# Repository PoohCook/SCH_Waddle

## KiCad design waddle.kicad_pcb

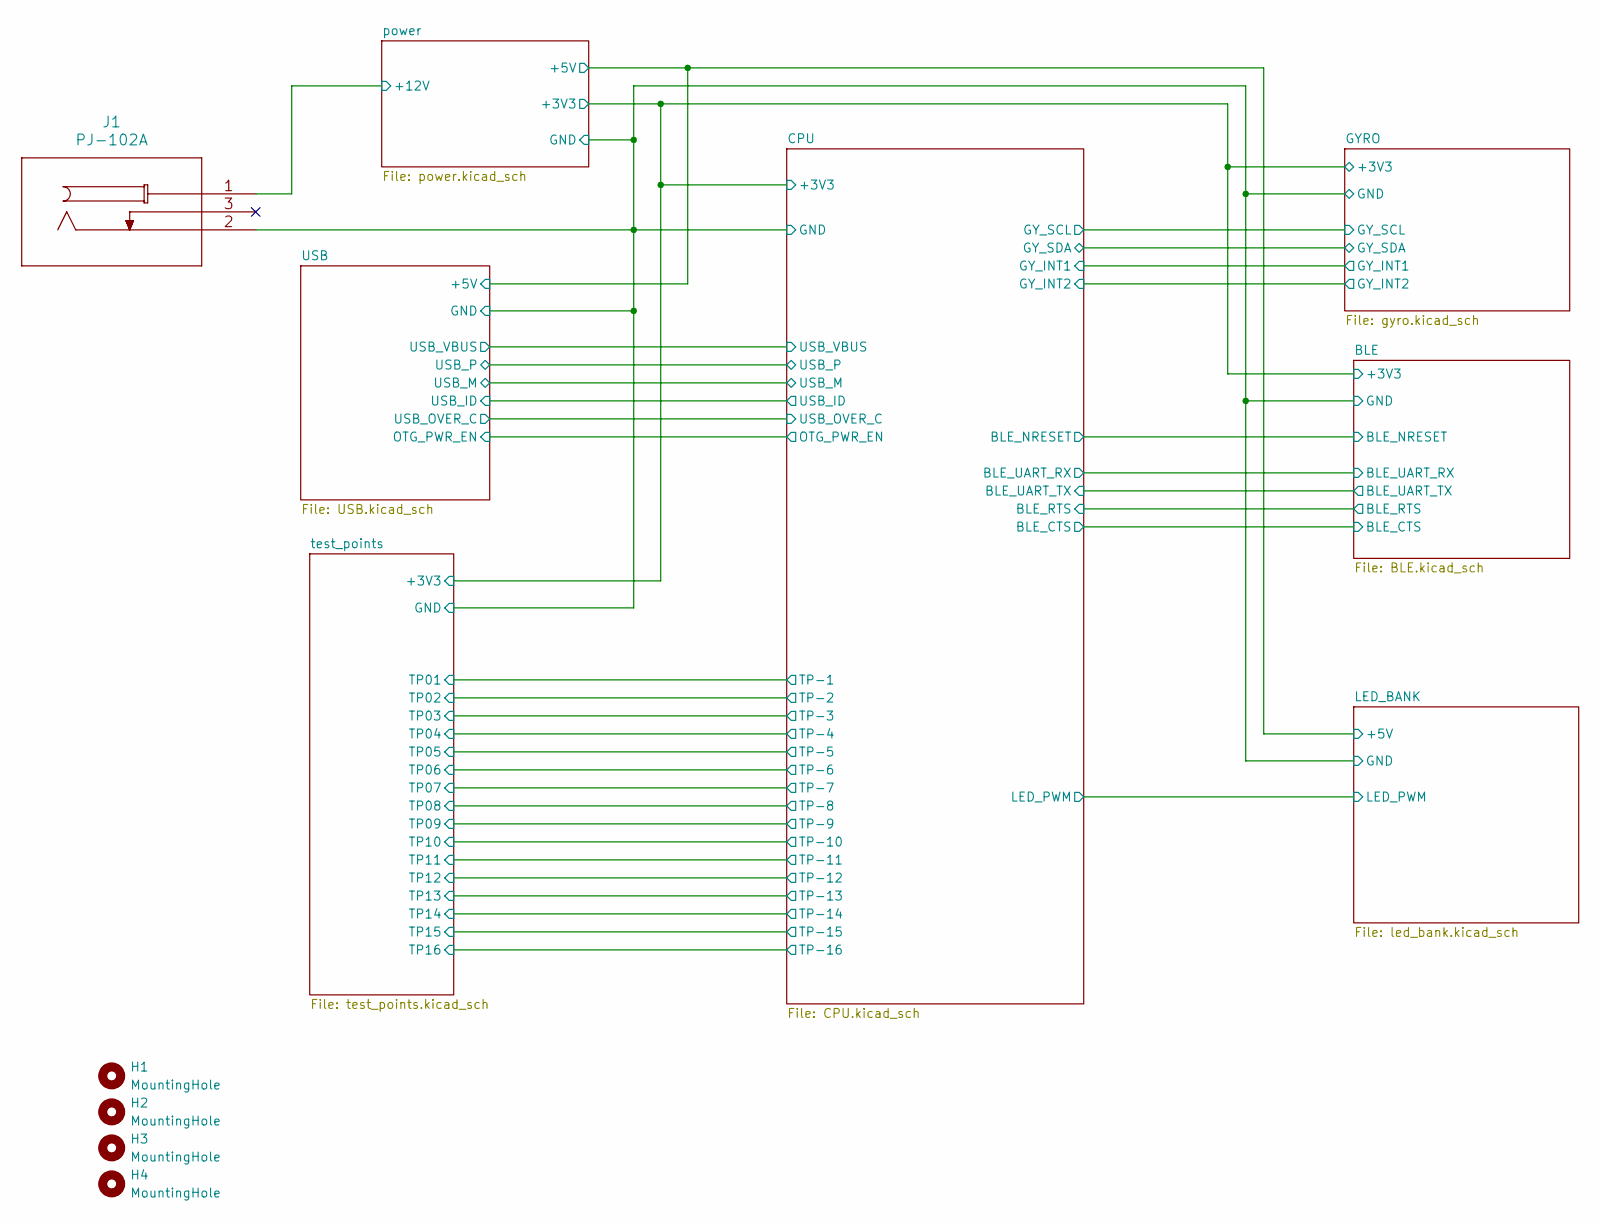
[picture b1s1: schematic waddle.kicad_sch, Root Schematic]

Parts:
H1, H2, H3, H4: MountingHole; MountingHole_2.7mm_M2.5_6mm_court
J1: PJ-102A; BarrelJack_CUI_PJ-102AH_Horizontal; PartNumber PJ-102A

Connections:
/power/+12V: J1.1; also elsewhere on the board

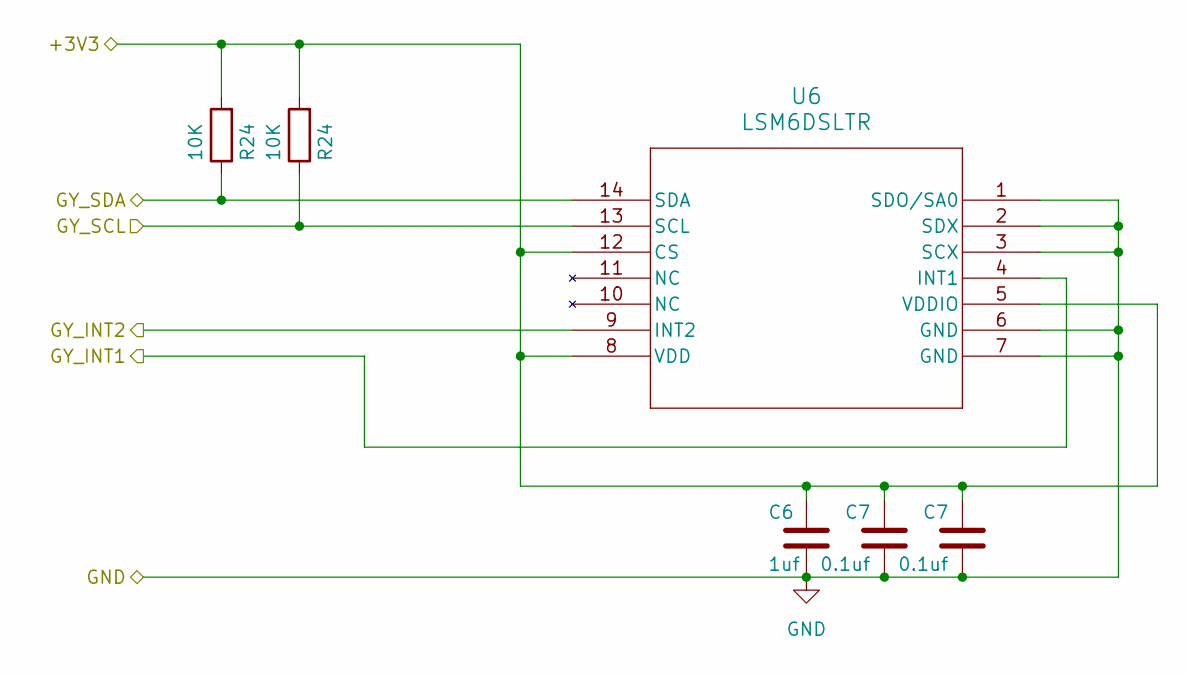
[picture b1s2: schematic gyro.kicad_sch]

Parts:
C6: 1uf; C_0603_1608Metric; PartNumber CL10A105KB8NNNC; LCSC Part Number C15849
C7: 0.1uf; C_0603_1608Metric; PartNumber CC0603KRX7R9BB104; LCSC Part Number C14663
R24: 10K; R_0603_1608Metric; PartNumber 0603WAF1002T5E; LCSC Part Number C25804
U6: LSM6DSLTR; QFN_6DSLTR_STM; PartNumber LSM6DSLTR; LCSC Part Number C126672

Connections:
/CPU/GY_INT1: U6.4 (INT1); also elsewhere on the board
/CPU/GY_INT2: U6.9 (INT2); also elsewhere on the board

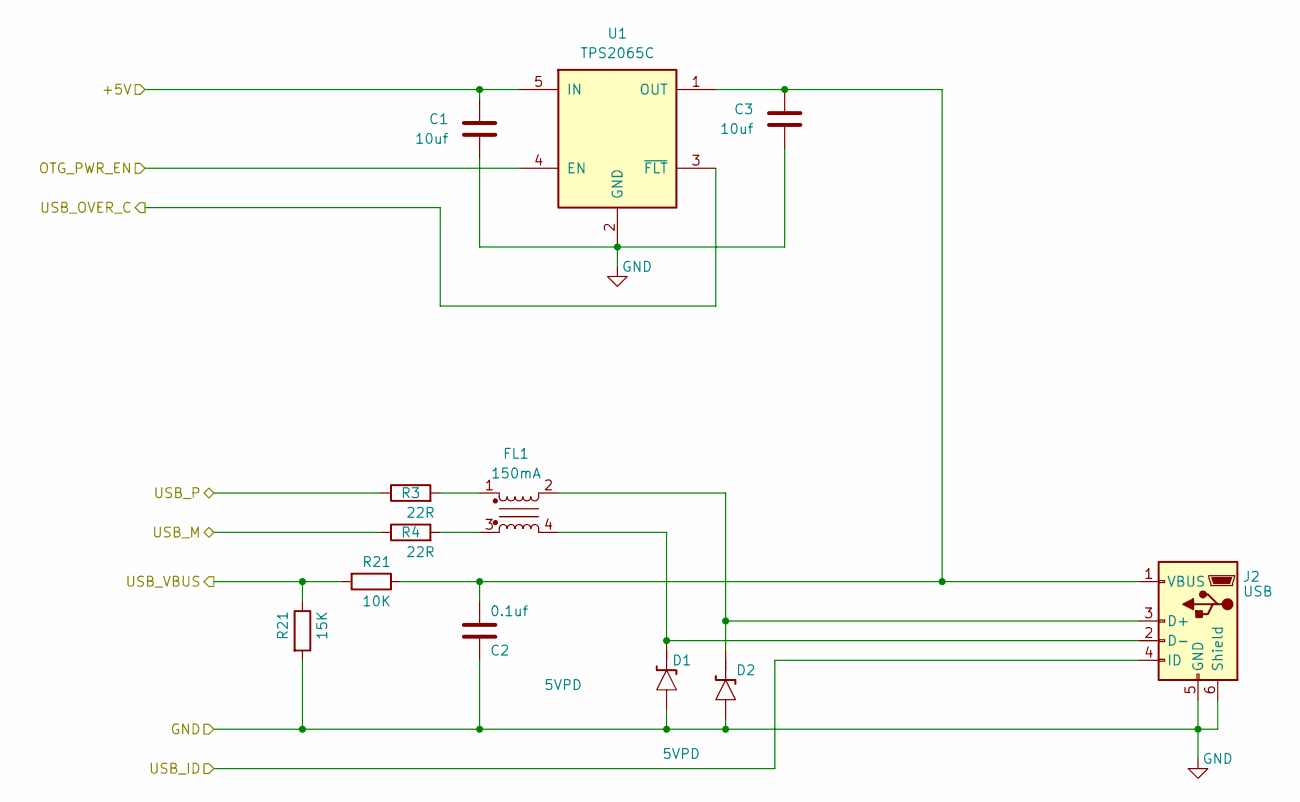
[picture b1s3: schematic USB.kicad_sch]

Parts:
C1, C3: 10uf; C_0603_1608Metric; PartNumber JMK107BJ106KA-T; LCSC Part Number C92782
C2: 0.1uf; C_0603_1608Metric; PartNumber CC0603KRX7R9BB104; LCSC Part Number C14663
D1, D2: 5VPD; D_SOD-923; PartNumber ESD9L5.0ST5G-P; LCSC Part Number C2912560
FL1: 150mA; DLP11SA900HL2L; PartNumber DLP11SA900HL2L; LCSC Part Number C76895
J2: USB; USB_MICRO_5.9mm; PartNumber MICRO5.9mmusb; LCSC Part Number C393940
R3, R4: 22R; R_0603_1608Metric; PartNumber 0603WAF220JT5E; LCSC Part Number C23345
R21: 15K; R_0603_1608Metric; PartNumber 0603WAF1502T5E; LCSC Part Number C22809
U1: TPS2065C; SOT-23-5; PartNumber TPS2065CDBVR; LCSC Part Number C353882

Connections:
/CPU/OTG_PWR_EN: U1.4 (EN); also elsewhere on the board
/CPU/USB_ID: J2.4 (ID); also elsewhere on the board
/CPU/USB_M: R4.1; also elsewhere on the board
/CPU/USB_OVER_C: U1.3 (~FLT); also elsewhere on the board
/CPU/USB_P: R3.1; also elsewhere on the board
unnamed: D1.1 (A1), FL1.4, J2.2 (D-)
unnamed: D2.1 (A1), FL1.2, J2.3 (D+)
unnamed: FL1.1, R3.2
unnamed: FL1.3, R4.2

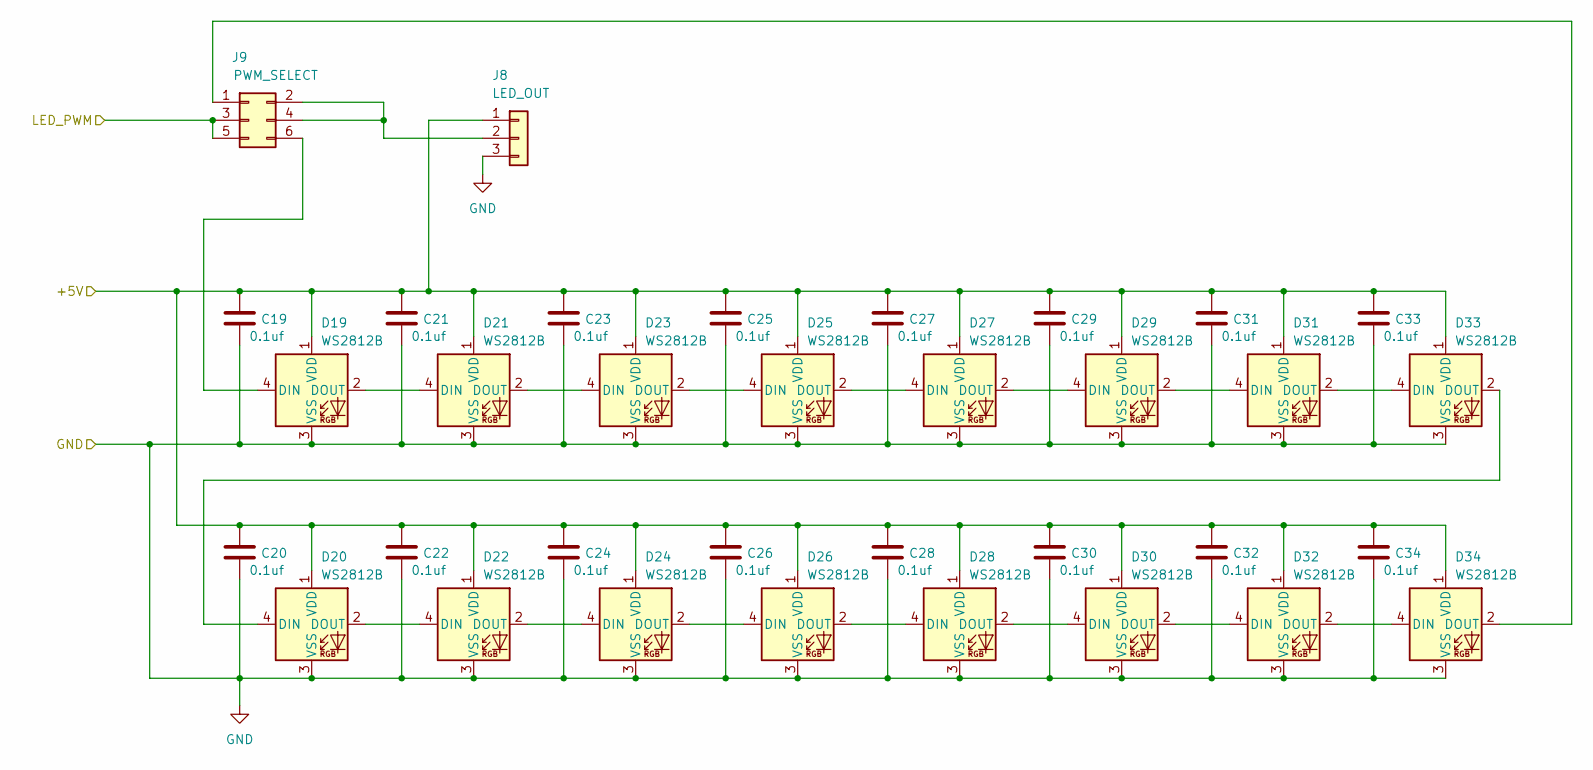
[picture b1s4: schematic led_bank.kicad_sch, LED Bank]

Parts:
C19, C20, C21, C22, C23, C24, C25, C26, C27, C28, C29, C30, C31, C32, C33, C34: 0.1uf; C_0603_1608Metric; PartNumber CC0603KRX7R9BB104; LCSC Part Number C14663
D19, D20, D21, D22, D23, D24, D25, D26, D27, D28, D29, D30, D31, D32, D33, D34: WS2812B; LED_WS2812B_PLCC4_5.0x5.0mm_P3.2mm; PartNumber WS2812B-B/T; LCSC Part Number C2761795
J8: LED_OUT; PinHeader_1x03_P2.54mm_Vertical
J9: PWM_SELECT; PinHeader_2x03_P2.54mm_Vertical

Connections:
/CPU/LED_PWM: J9.3, J9.5; also elsewhere on the board
unnamed: D19.4 (DIN), J9.6
unnamed: D19.2 (DOUT), D21.4 (DIN)
unnamed: D20.4 (DIN), D33.2 (DOUT)
unnamed: D20.2 (DOUT), D22.4 (DIN)
unnamed: D21.2 (DOUT), D23.4 (DIN)
unnamed: D22.2 (DOUT), D24.4 (DIN)
unnamed: D23.2 (DOUT), D25.4 (DIN)
unnamed: D24.2 (DOUT), D26.4 (DIN)
unnamed: D25.2 (DOUT), D27.4 (DIN)
unnamed: D26.2 (DOUT), D28.4 (DIN)
unnamed: D27.2 (DOUT), D29.4 (DIN)
unnamed: D28.2 (DOUT), D30.4 (DIN)
unnamed: D29.2 (DOUT), D31.4 (DIN)
unnamed: D30.2 (DOUT), D32.4 (DIN)
unnamed: D31.2 (DOUT), D33.4 (DIN)
unnamed: D32.2 (DOUT), D34.4 (DIN)
unnamed: D34.2 (DOUT), J9.1
unnamed: J8.2, J9.2, J9.4

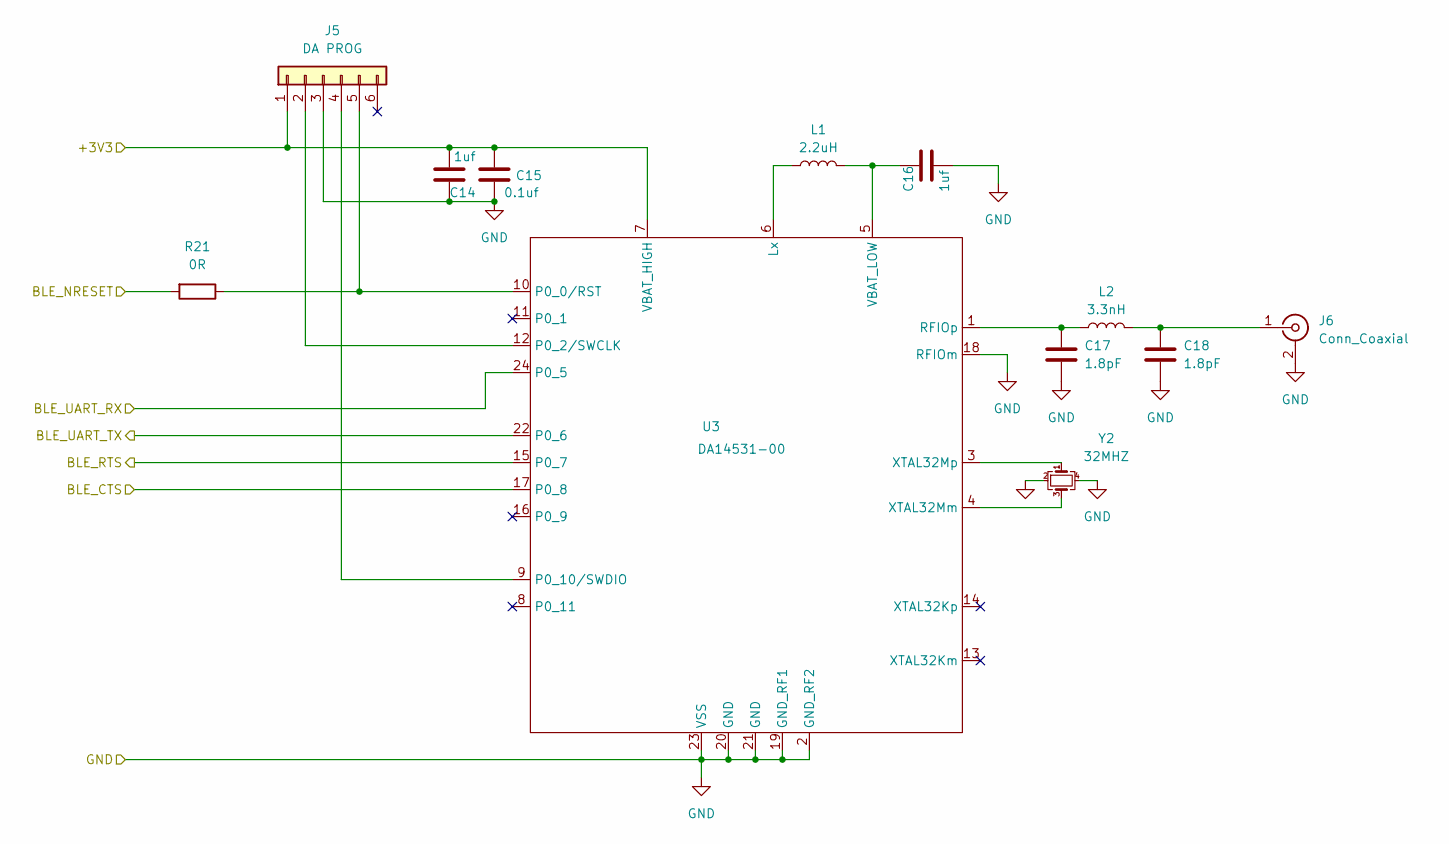
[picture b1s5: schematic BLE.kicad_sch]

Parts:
C14, C16: 1uf; C_0603_1608Metric; PartNumber CL10A105KB8NNNC; LCSC Part Number C15849
C15: 0.1uf; C_0603_1608Metric; PartNumber CC0603KRX7R9BB104; LCSC Part Number C14663
C17, C18: 1.8pF; C_0603_1608Metric; PartNumber FN18N1R8B500PSG; LCSC Part Number C565610
J5: DA PROG; CONN_20021221-00006T4LF_AMP
J6: Conn_Coaxial; SMA_EdgeMount_Horizontal; PartNumber SMA-KE-P903; LCSC Part Number C914558
L1: 2.2uH; L_0603_1608Metric; PartNumber MPL1608S2R2MHT; LCSC Part Number C98327
L2: 3.3nH; L_0603_1608Metric; PartNumber FHW0603UC3N3KST; LCSC Part Number C317981
R21: 0R; R_0603_1608Metric; PartNumber RS-03000JT; LCSC Part Number C115304
U3: DA14531-00; FCGQFN24
Y2: 32MHZ; Crystal_SMD_3225-4Pin_3.2x2.5mm; PartNumber TZ0375B; LCSC Part Number C498199

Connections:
/BLE/BLE_CTS: U3.17 (P0_8); also elsewhere on the board
/BLE/BLE_RTS: U3.15 (P0_7); also elsewhere on the board
/BLE/BLE_UART_RX: U3.24 (P0_5); also elsewhere on the board
/BLE/BLE_UART_TX: U3.22 (P0_6); also elsewhere on the board
unnamed: J5.2, U3.12 (P0_2/SWCLK)
unnamed: J5.4, U3.9 (P0_10/SWDIO)
unnamed: C18.1, J6.1 (In), L2.2
unnamed: L1.1, U3.6 (Lx)
unnamed: C17.1, L2.1, U3.1 (RFIOp)
unnamed: C16.1, L1.2, U3.5 (VBAT_LOW)
unnamed: U3.4 (XTAL32Mm), Y2.3
unnamed: U3.3 (XTAL32Mp), Y2.1

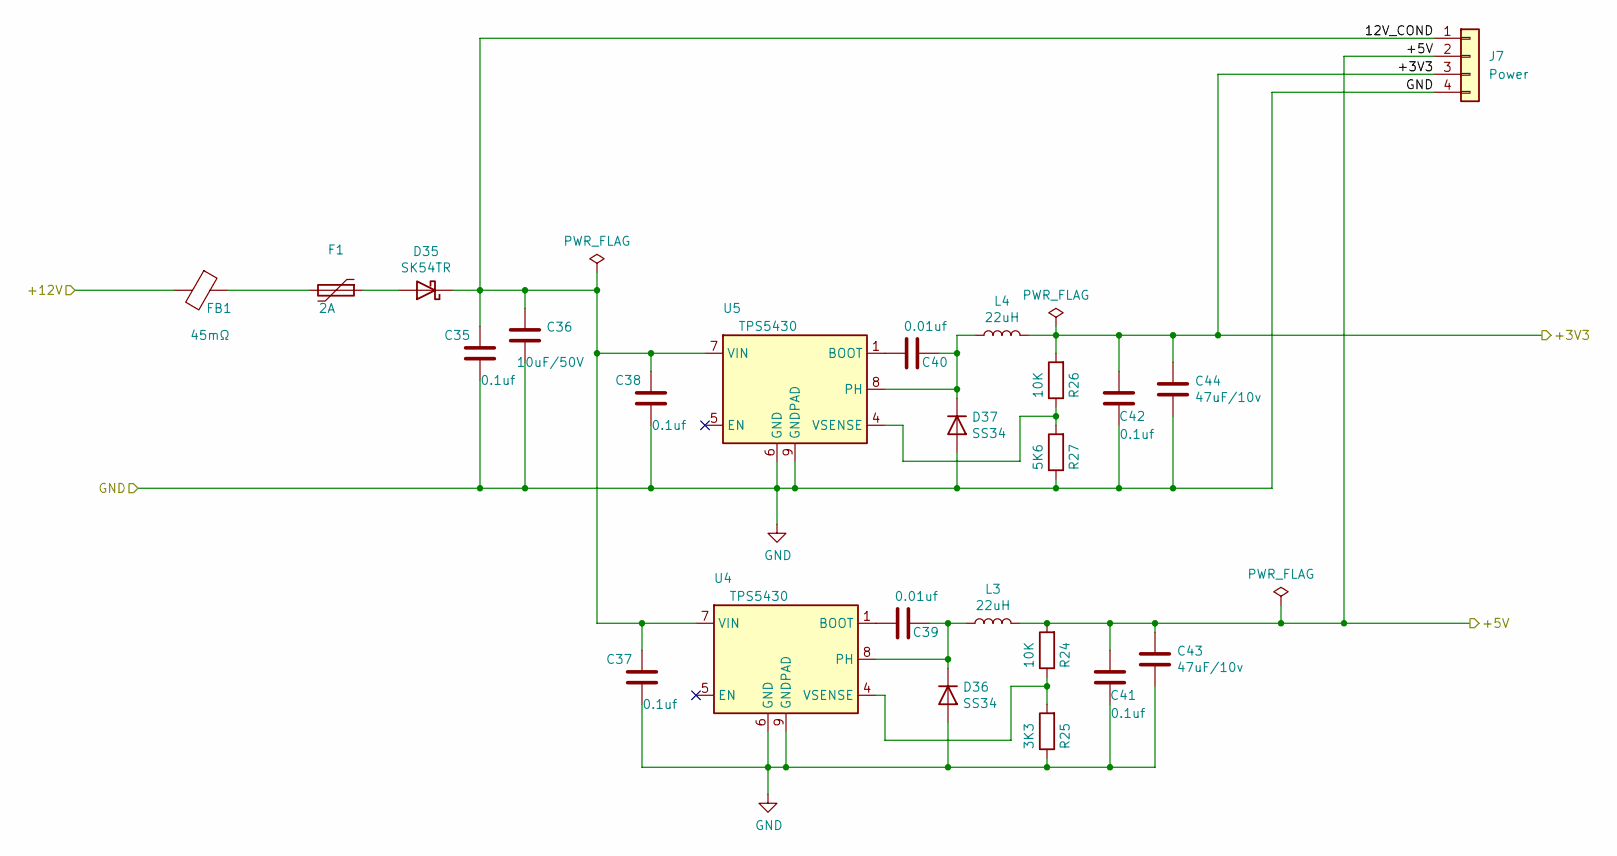
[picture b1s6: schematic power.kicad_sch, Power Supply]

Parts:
C35, C37, C38, C41, C42: 0.1uf; C_0603_1608Metric; PartNumber CC0603KRX7R9BB104; LCSC Part Number C14663
C36: 10uF/50V; C_1206_3216Metric; PartNumber CL31A106KBHNNNE; LCSC Part Number C13585
C39, C40: 0.01uf; C_0603_1608Metric; PartNumber 0603B103K101CT; LCSC Part Number C302008
C43, C44: 47uF/10v; C_1206_3216Metric; PartNumber CL31A476MPHNNNE; LCSC Part Number C96123
D35: SK54TR; D_SMB; PartNumber SS54-SMB; LCSC Part Number C908685
D36, D37: SS34; D_SMA; PartNumber SS34; LCSC Part Number C8678
F1: 2A; R_1206_3216Metric; PartNumber BSMD1206-100-24V; LCSC Part Number C910830
FB1: 45mΩ; R_0805_2012Metric; PartNumber BLM21PG221SN1D; LCSC Part Number C85840
J7: Power; PinHeader_1x04_P2.54mm_Vertical
L3, L4: 22uH; L_7.3x7.3_Bourne; PartNumber SWPA6045S220MT; LCSC Part Number C83454
R24, R26: 10K; R_0603_1608Metric; PartNumber 0603WAF1002T5E; LCSC Part Number C25804
R25: 3K3; R_0603_1608Metric; PartNumber 0603WAF3301T5E; LCSC Part Number C22978
R27: 5K6; R_0603_1608Metric; PartNumber RS-03K5601FT; LCSC Part Number C99891
U4, U5: TPS5430; HSOP-8-1EP_3.9x4.9mm_P1.27mm_EP2.41x3.1mm_ThermalVias; PartNumber TPS5430DDAR; LCSC Part Number C9864

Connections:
/power/12V_COND: C35.1, C36.1, C37.1, C38.1, D35.1 (K), J7.1, U4.7 (VIN), U5.7 (VIN)
/power/+12V: FB1.2; also elsewhere on the board
unnamed: D35.2 (A), F1.1
unnamed: C39.1, D36.1 (K), L3.1, U4.8 (PH)
unnamed: C40.1, D37.1 (K), L4.1, U5.8 (PH)
unnamed: F1.2, FB1.1
unnamed: C39.2, U4.1 (BOOT)
unnamed: C40.2, U5.1 (BOOT)
unnamed: R26.1, R27.2, U5.4 (VSENSE)

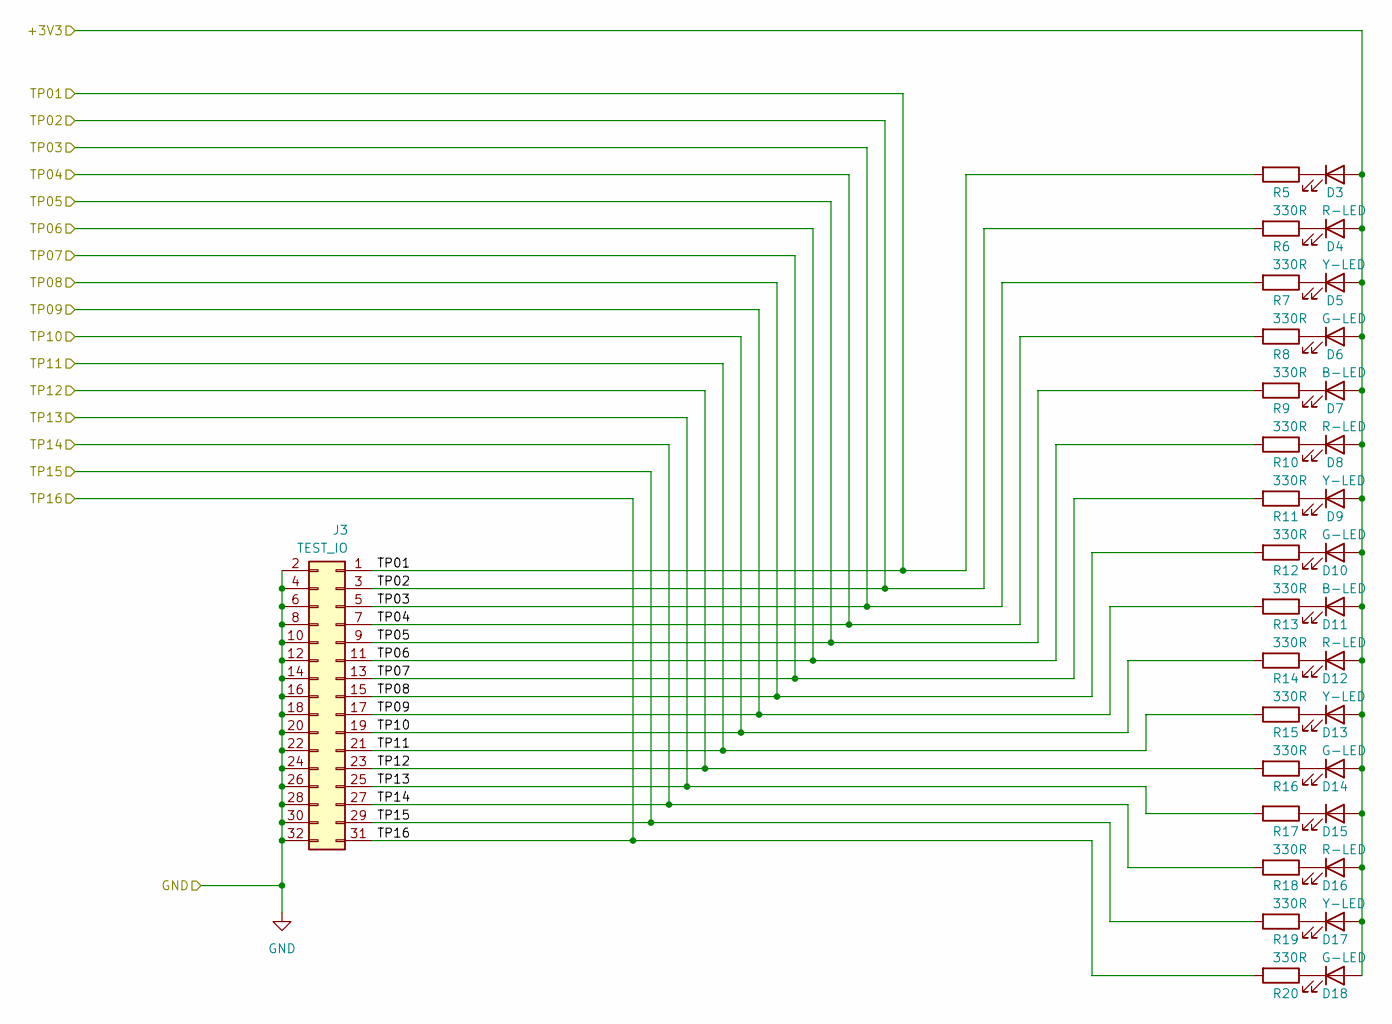
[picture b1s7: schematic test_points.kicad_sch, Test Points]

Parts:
D3, D7, D11, D15: R-LED; D_0603_1608Metric; PartNumber KT-0603R; LCSC Part Number C2286
D4, D8, D12, D16: Y-LED; D_0603_1608Metric; PartNumber 19-213/Y2C-CQ2R2L/3T(CY); LCSC Part Number C72038
D5, D9, D13, D17: G-LED; D_0603_1608Metric; PartNumber 19-217/GHC-YR1S2/3T; LCSC Part Number C72043
D6, D10, D14, D18: B-LED; D_0603_1608Metric; PartNumber 19-217/BHC-ZL1M2RY/3T; LCSC Part Number C72041
J3: TEST_IO; PinHeader_2x16_P2.54mm_Vertical
R5, R6, R7, R8, R9, R10, R11, R12, R13, R14, R15, R16, R17, R18, R19, R20: 330R; R_0603_1608Metric; PartNumber 0603WAF3300T5E; LCSC Part Number C23138

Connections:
/test_points/TP01: J3.1, R5.2; also elsewhere on the board
/test_points/TP02: J3.3, R6.2; also elsewhere on the board
/test_points/TP03: J3.5, R7.2; also elsewhere on the board
/test_points/TP04: J3.7, R8.2; also elsewhere on the board
/test_points/TP05: J3.9, R9.2; also elsewhere on the board
/test_points/TP06: J3.11, R10.2; also elsewhere on the board
/test_points/TP07: J3.13, R11.2; also elsewhere on the board
/test_points/TP08: J3.15, R12.2; also elsewhere on the board
/test_points/TP09: J3.17, R13.2; also elsewhere on the board
/test_points/TP10: J3.19, R14.2; also elsewhere on the board
/test_points/TP11: J3.21, R15.2; also elsewhere on the board
/test_points/TP12: J3.23, R16.2; also elsewhere on the board
/test_points/TP13: J3.25, R17.2; also elsewhere on the board
/test_points/TP14: J3.27, R18.2; also elsewhere on the board
/test_points/TP15: J3.29, R19.2; also elsewhere on the board
/test_points/TP16: J3.31, R20.2; also elsewhere on the board
unnamed: D3.1 (K), R5.1
unnamed: D4.1 (K), R6.1
unnamed: D5.1 (K), R7.1
unnamed: D6.1 (K), R8.1
unnamed: D7.1 (K), R9.1
unnamed: D8.1 (K), R10.1
unnamed: D9.1 (K), R11.1
unnamed: D10.1 (K), R12.1
unnamed: D11.1 (K), R13.1
unnamed: D12.1 (K), R14.1
unnamed: D13.1 (K), R15.1
unnamed: D14.1 (K), R16.1
unnamed: D15.1 (K), R17.1
unnamed: D16.1 (K), R18.1
unnamed: D17.1 (K), R19.1
unnamed: D18.1 (K), R20.1

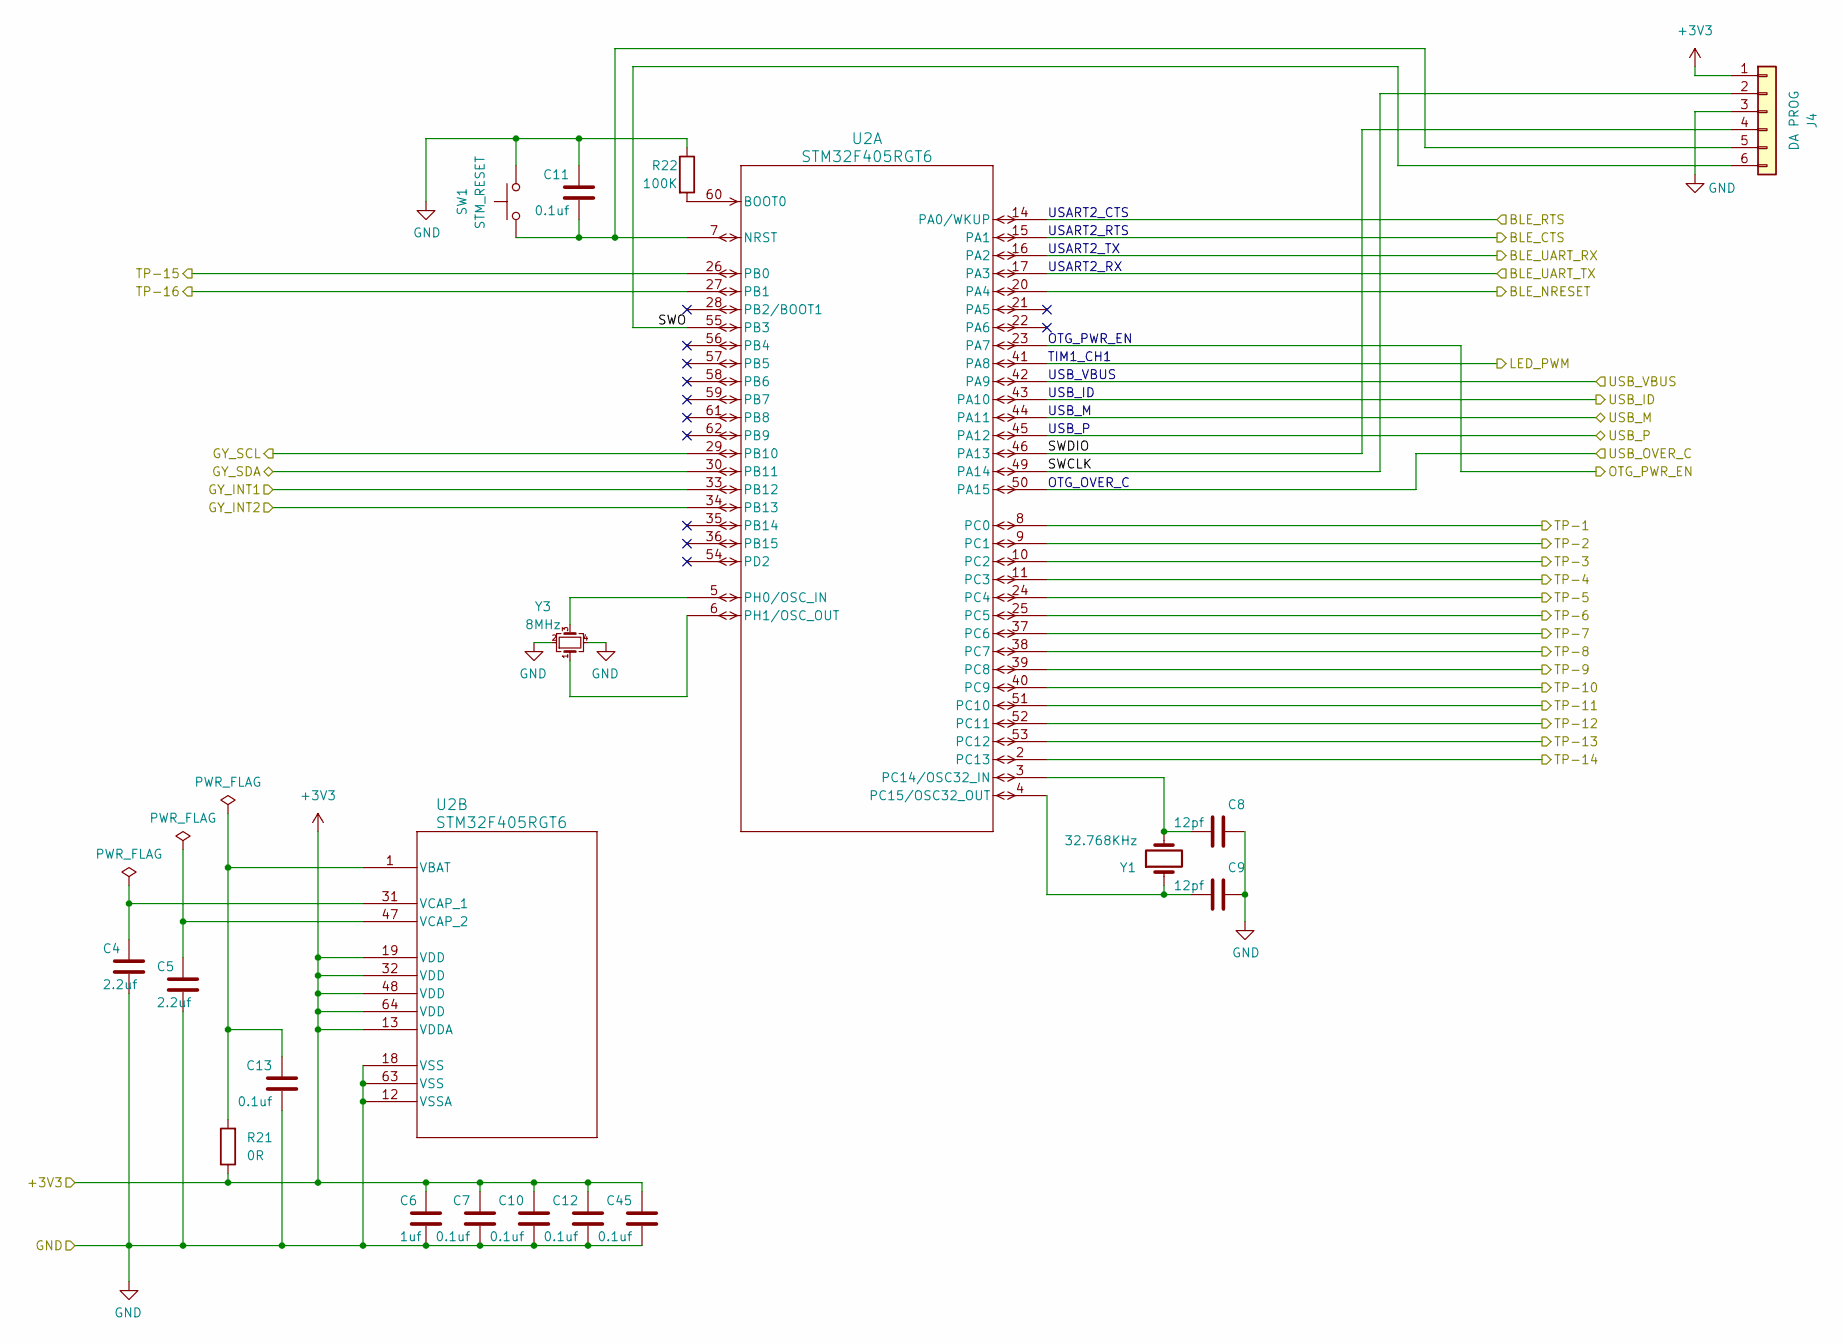
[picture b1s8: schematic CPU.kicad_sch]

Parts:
C4, C5: 2.2uf; C_0603_1608Metric; PartNumber CL10A225KO8NNNC; LCSC Part Number C23630
C6: 1uf; C_0603_1608Metric; PartNumber CL10A105KB8NNNC; LCSC Part Number C15849
C7, C10, C11, C12, C13, C45: 0.1uf; C_0603_1608Metric; PartNumber CC0603KRX7R9BB104; LCSC Part Number C14663
C8, C9: 12pf; C_0603_1608Metric; PartNumber TCC0603COG120J500CT; LCSC Part Number C376767
J4: DA PROG; CONN_20021221-00006T4LF_AMP
R21: 0R; R_0603_1608Metric; PartNumber RS-03000JT; LCSC Part Number C115304
R22: 100K; R_0603_1608Metric; PartNumber 0603WAF1003T5E; LCSC Part Number C25803
SW1: STM_RESET; SW-4_5.1x5.1x2.5; PartNumber TS-1187A-C-E-B; LCSC Part Number C318887
U2: STM32F405RGT6; LQFP-64_10x10mm_P0.5mm; PartNumber STM32F405RGT6; LCSC Part Number C15742
Y1: 32.768KHz; Crystal_SMD_3215-2Pin_3.2x1.5mm; PartNumber CM7V-T1A-32.768KHZ-12.5PF; LCSC Part Number C48615
Y3: 8MHz; Crystal_SMD_3225-4Pin_3.2x2.5mm; PartNumber WTL3M28285LZ; LCSC Part Number C2857622

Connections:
/BLE/BLE_CTS: U2.15 (PA1); also elsewhere on the board
/BLE/BLE_NRESET: U2.20 (PA4); also elsewhere on the board
/BLE/BLE_RTS: U2.14 (PA0/WKUP); also elsewhere on the board
/BLE/BLE_UART_RX: U2.16 (PA2); also elsewhere on the board
/BLE/BLE_UART_TX: U2.17 (PA3); also elsewhere on the board
/CPU/GY_INT1: U2.33 (PB12); also elsewhere on the board
/CPU/GY_INT2: U2.34 (PB13); also elsewhere on the board
/CPU/LED_PWM: U2.41 (PA8); also elsewhere on the board
/CPU/OTG_PWR_EN: U2.23 (PA7); also elsewhere on the board
/CPU/SWCLK: J4.2, U2.49 (PA14)
/CPU/SWDIO: J4.4, U2.46 (PA13)
/CPU/SWO: J4.6, U2.55 (PB3)
/CPU/USB_ID: U2.43 (PA10); also elsewhere on the board
/CPU/USB_M: U2.44 (PA11); also elsewhere on the board
/CPU/USB_OVER_C: U2.50 (PA15); also elsewhere on the board
/CPU/USB_P: U2.45 (PA12); also elsewhere on the board
/CPU/USB_VBUS: U2.42 (PA9); also elsewhere on the board
/test_points/TP01: U2.8 (PC0); also elsewhere on the board
/test_points/TP02: U2.9 (PC1); also elsewhere on the board
/test_points/TP03: U2.10 (PC2); also elsewhere on the board
/test_points/TP04: U2.11 (PC3); also elsewhere on the board
/test_points/TP05: U2.24 (PC4); also elsewhere on the board
/test_points/TP06: U2.25 (PC5); also elsewhere on the board
/test_points/TP07: U2.37 (PC6); also elsewhere on the board
/test_points/TP08: U2.38 (PC7); also elsewhere on the board
/test_points/TP09: U2.39 (PC8); also elsewhere on the board
/test_points/TP10: U2.40 (PC9); also elsewhere on the board
/test_points/TP11: U2.51 (PC10); also elsewhere on the board
/test_points/TP12: U2.52 (PC11); also elsewhere on the board
/test_points/TP13: U2.53 (PC12); also elsewhere on the board
/test_points/TP14: U2.2 (PC13); also elsewhere on the board
/test_points/TP15: U2.26 (PB0); also elsewhere on the board
/test_points/TP16: U2.27 (PB1); also elsewhere on the board
unnamed: C11.2, J4.5, SW1.1, U2.7 (NRST)
unnamed: R22.2, U2.60 (BOOT0)
unnamed: C8.1, U2.3 (PC14/OSC32_IN), Y1.2
unnamed: C9.1, U2.4 (PC15/OSC32_OUT), Y1.1
unnamed: U2.5 (PH0/OSC_IN), Y3.3
unnamed: U2.6 (PH1/OSC_OUT), Y3.1
unnamed: C4.1, U2.31 (VCAP_1)
unnamed: C5.1, U2.47 (VCAP_2)

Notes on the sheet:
USART2_RTS
USB_VBUS
OTG_PWR_EN
USART2_TX
USART2_CTS
USB_ID
OTG_OVER_C
USART2_RX
USB_M
TIM1_CH1
USB_P

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
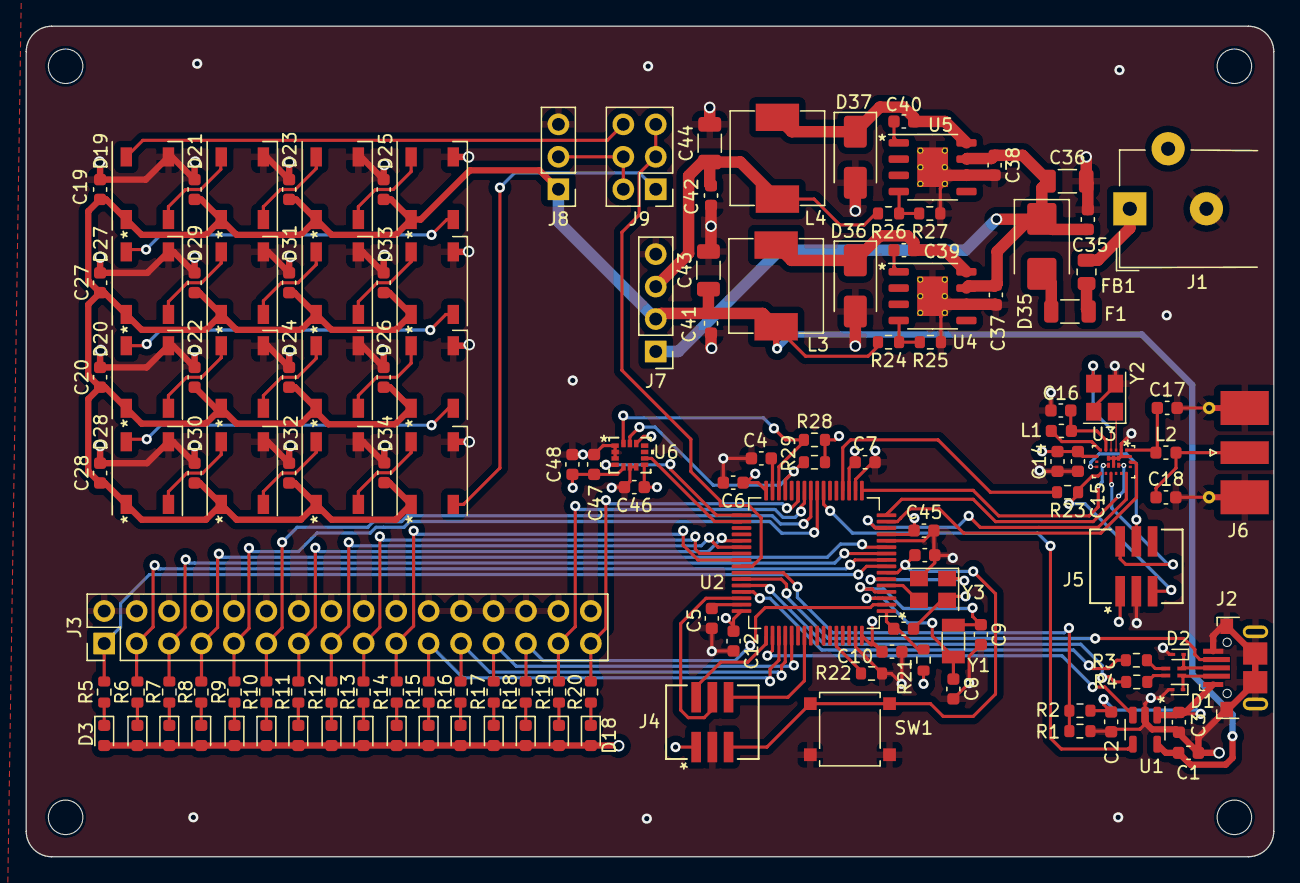
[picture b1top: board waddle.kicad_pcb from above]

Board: 4 copper layers, 97.7 x 65.0 mm, 144 parts (0 on the bottom side), 105 nets.

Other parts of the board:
C46: 1uf; C_0603_1608Metric
C47, C48: 0.1uf; C_0603_1608Metric
R1: 15K; R_0603_1608Metric
R2, R28, R29: 10K; R_0603_1608Metric
R23: 0R; R_0603_1608Metric

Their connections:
/BLE/BLE_NRESET: R23.2; also elsewhere on the board
/CPU/USB_VBUS: R1.1, R2.2; also elsewhere on the board

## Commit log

2024-01-10 initial put
